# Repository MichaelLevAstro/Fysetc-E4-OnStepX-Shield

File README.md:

# Shield for adding Extra modules to FYSETC E4 Board

## Added features
- GPS through X-Min pin
- MCP23017 IO expander for homing sensors using I2C
- FRAM for persistent data
- 5V Laser with Switch
- 12v to 24v step up module for a Motor Brake using an XL6009 module

Links to modules:
FRAM:
https://www.aliexpress.com/item/1005006584211412.html?sk=6mia6uv

MCP23017:
https://www.aliexpress.com/item/1005005335661057.html?spm=a2g0o.order_list.order_list_main.26.48951802nkMEFA

DC Step up:
https://www.aliexpress.com/item/32762092828.html?spm=a2g0o.order_list.order_list_main.37.48951802nkMEFA

Home sensors i used (Wide body):
https://www.aliexpress.com/item/32990256417.html?spm=a2g0o.order_list.order_list_main.58.48951802nkMEFA

GPS:
https://www.aliexpress.com/item/1005006495592091.html?spm=a2g0o.order_list.order_list_main.47.48951802nkMEFA
*note: any GPS using a TX should work (as long as it works with TinyGPS++)
*note2: GPS is very sensitive and often can communicate with enough satellites and cant get a fix, up to you to make it work properly in your enclosure.

Laser:
Any 5v laser should work fine

# OnStepX configurations
In config.h

```
#define LIMIT_SENSE_PIN                 0 // Set this to 0 or even comment it out, wont be used

// FRAM
#define NV_DRIVER             NV_MB85RC64

// Homing sensors
#define AXIS1_SENSE_HOME             HIGH
#define AXIS2_SENSE_HOME             HIGH

// GPS
#define TIME_LOCATION_SOURCE          GPS
#define SERIAL_GPS SoftSerial
#define SERIAL_GPS_RX 34
#define SERIAL_GPS_TX 0 // must be set or wont compile
#define SERIAL_GPS_BAUD 9600
```

In src\pinmaps\Pins.FYSETC_E4.h:
```
// Needed for IO expander to work
#define AXIS1_SENSE_HOME_PIN  GPIO_PIN(0)
#define AXIS2_SENSE_HOME_PIN   GPIO_PIN(1)
```

# Connections

*note: X-Min connector in the shield is a 2 pin connector, you dont have to connect GND, you can connect only the X-Min.

# Assembly
I used M3 standoffs, and removed anything tall from the board, the original heatsinks for the motors drivers and the green power connectors.
Had to make room to fit in my mount.

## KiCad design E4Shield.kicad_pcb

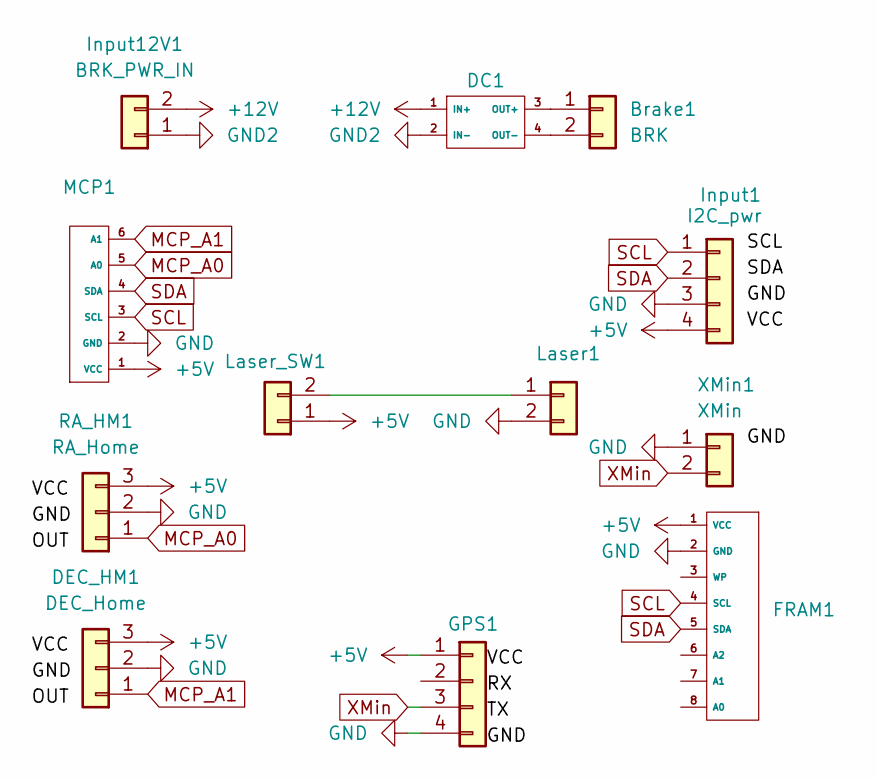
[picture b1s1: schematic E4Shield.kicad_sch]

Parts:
Brake1: BRK; JST_XH_B2B-XH-A_1x02_P2.50mm_Vertical
DC1: XL6009E1
DEC_HM1: DEC_Home; JST_XH_B3B-XH-A_1x03_P2.50mm_Vertical
FRAM1: FRAM_MB85RC256V
GPS1: Conn_01x04; JST_XH_B4B-XH-A_1x04_P2.50mm_Vertical
Input1: I2C_pwr; JST_XH_B4B-XH-A_1x04_P2.50mm_Vertical
Input12V1: BRK_PWR_IN; JST_XH_B2B-XH-A_1x02_P2.50mm_Vertical
Laser1: Conn_01x02; JST_XH_B2B-XH-A_1x02_P2.50mm_Vertical
Laser_SW1: Conn_01x02; JST_XH_B2B-XH-A_1x02_P2.50mm_Vertical
MCP1: MCP23017_Module
RA_HM1: RA_Home; JST_XH_B3B-XH-A_1x03_P2.50mm_Vertical
XMin1: XMin; JST_XH_B2B-XH-A_1x02_P2.50mm_Vertical

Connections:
+5V: DEC_HM1.3, FRAM1.1 (VCC), GPS1.1, Input1.4, Laser_SW1.1, MCP1.1 (VCC), RA_HM1.3
+12V: DC1.1 (IN+), Input12V1.2
GND: DEC_HM1.2, FRAM1.2 (GND), GPS1.4, Input1.3, Laser1.2, MCP1.2 (GND), RA_HM1.2, XMin1.1
GND2: DC1.2 (IN-), Input12V1.1
MCP_A0: MCP1.5 (A0), RA_HM1.1
MCP_A1: DEC_HM1.1, MCP1.6 (A1)
unnamed: Brake1.1, DC1.3 (OUT+)
unnamed: Brake1.2, DC1.4 (OUT-)
unnamed: Laser1.1, Laser_SW1.2
SCL: FRAM1.4 (SCL), Input1.1, MCP1.3 (SCL)
SDA: FRAM1.5 (SDA), Input1.2, MCP1.4 (SDA)
XMin: GPS1.3, XMin1.2

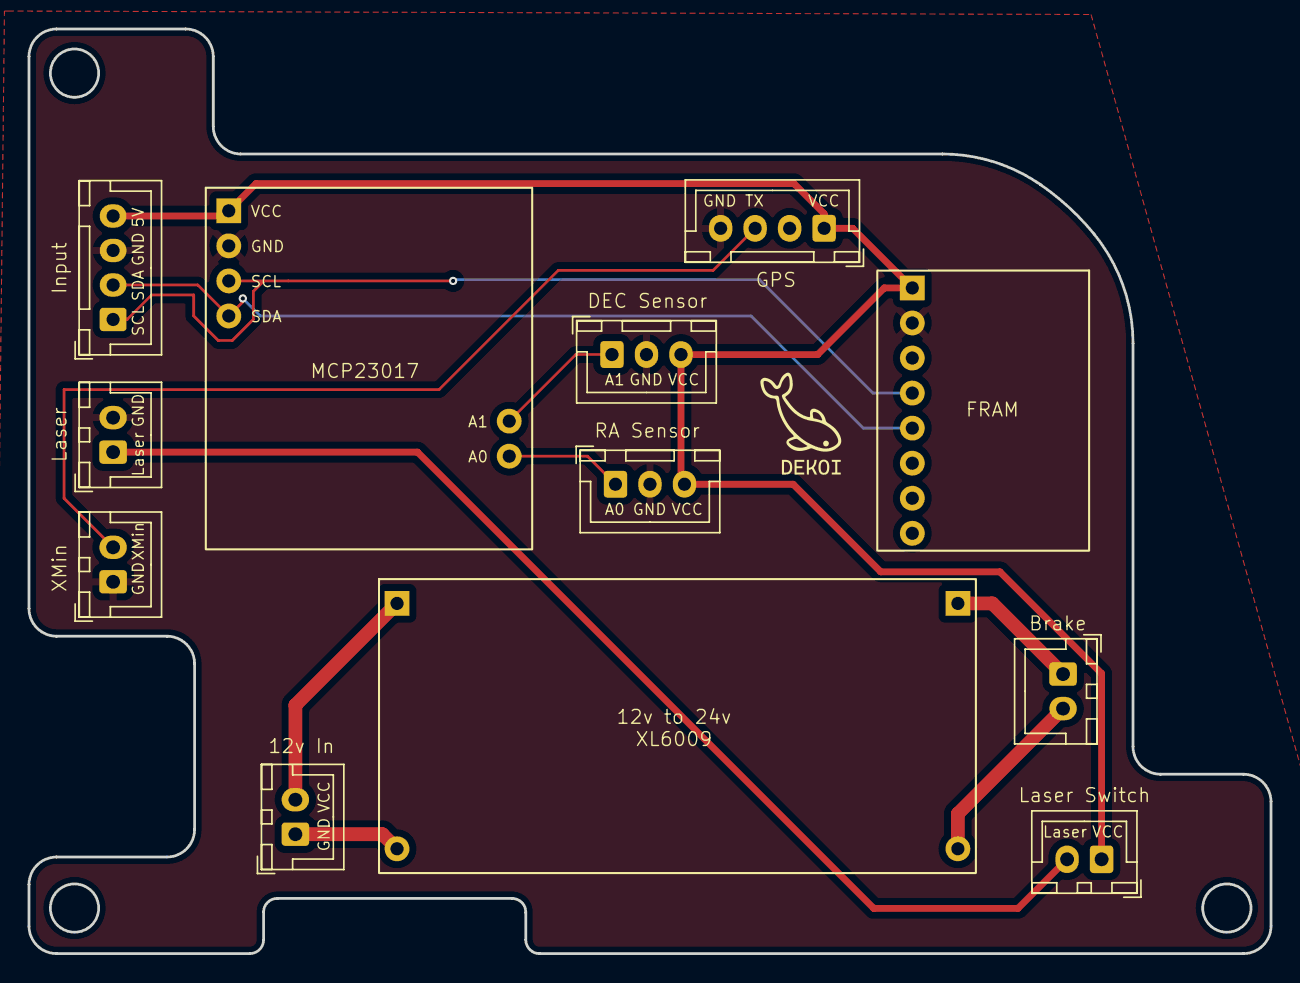
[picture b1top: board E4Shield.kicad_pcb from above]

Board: 2 copper layers, 90.0 x 67.0 mm, 12 parts (0 on the bottom side), 12 nets.

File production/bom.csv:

Designator,Footprint,Quantity,Value,LCSC Part #
BRAKE1,JST_XH_B2B-XH-A_1x02_P2.50mm_Vertical,1,BRK,
DC1,XL6009E1,1,~,
FRAM1,FRAM_MB85RC256V,1,~,
GPS1,JST_XH_B4B-XH-A_1x04_P2.50mm_Vertical,1,Conn_01x04,
INPUT1,JST_XH_B4B-XH-A_1x04_P2.50mm_Vertical,1,I2C_pwr,
INPUT12V1,JST_XH_B2B-XH-A_1x02_P2.50mm_Vertical,1,BRK_PWR_IN,
"LASER1, LASER_SW1",JST_XH_B2B-XH-A_1x02_P2.50mm_Vertical,2,Conn_01x02,
MCP1,MCP23017_Module,1,~,
XMIN1,JST_XH_B2B-XH-A_1x02_P2.50mm_Vertical,1,XMin,
X_HM1,JST_XH_B3B-XH-A_1x03_P2.50mm_Vertical,1,X_Home,
Y_HM1,JST_XH_B3B-XH-A_1x03_P2.50mm_Vertical,1,Y_Home,

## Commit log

2025-08-05 Initial
2025-08-05 Ready gerber zips
